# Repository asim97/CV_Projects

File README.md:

**WARNINIG**:
- this resp contains parts from bigger projects.
- this resp contains *only* embededd related projects, more projects are NOT included.
- *MOST* of libiries used in Skatchs are either modfied or originaly-writen to serve its pourpose in thier APP.
- no warranty grunted,use any parts of the code at your OWN risk.

**REQUIRMMENTS**:
- NI LABVIEW 2018
- Proutes 8.6
- Autodesk Eagle 8.5.6
- Arduino IDE 1.8.10
- SkethUP 2017
- ECLIPSE 2018

**NOTE**
	I used Arduino IDE as my main IDE for its simpelsty and easyly to compile the code to AVRs,ARMs,ESPs ...
	Eclipse was used at first, for  SVN and github only 
	since i was working alone... no need for the heavy interface for ECLIPSE

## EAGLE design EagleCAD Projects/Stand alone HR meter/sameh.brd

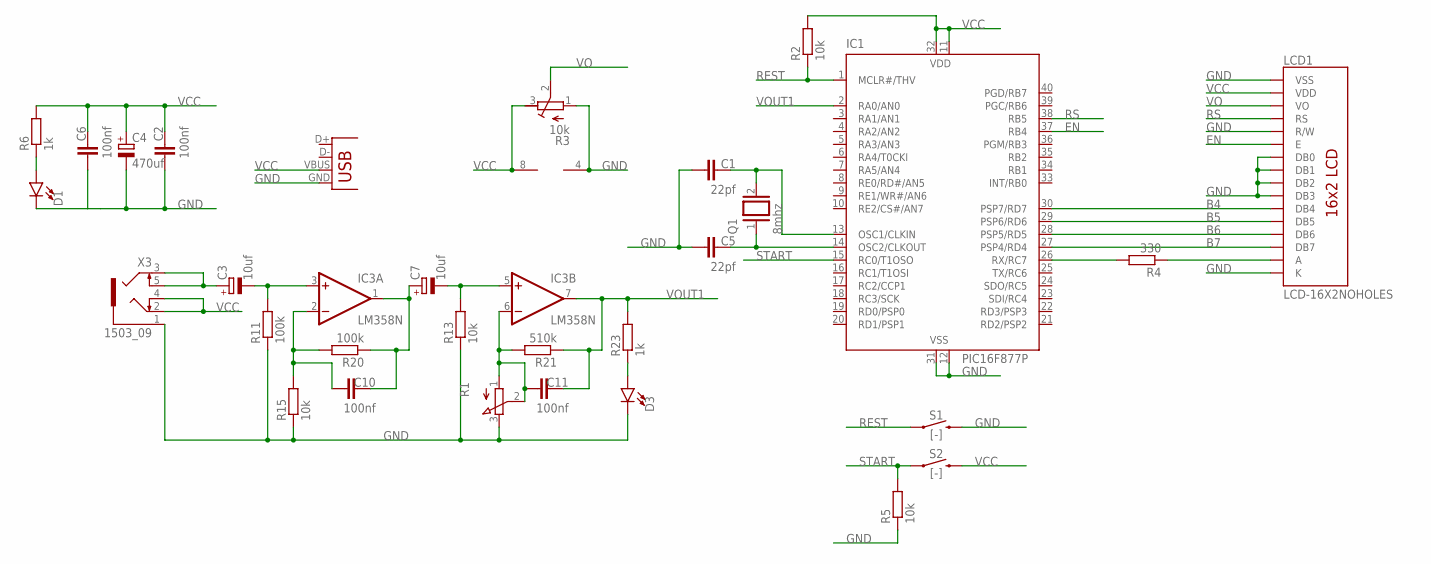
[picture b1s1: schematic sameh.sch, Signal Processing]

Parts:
C1, C5: 22pf; C050-030X075
C2, C6, C10, C11: 100nf; C050-030X075
C3, C7: 10uf; E2-5
C4: 470uf; E3,5-8
D1, D3: LED5MM; LED_5MM
IC1: PIC16F877P; DIL40
IC3: LM358N; DIL08
LCD1: LCD-16X2NOHOLES; LCD-16X2_NOHOLESNOSILK
Q1: 8mhz; QS
R1: 3RP/1610N
R2, R5, R13, R15: 10k; 0207/10
R3: 10k; RTRIM64W
R4: 330; 0207/10
R6, R23: 1k; 0207/10
R11, R20: 100k; 0207/10
R21: 510k; 0207/10
S1, S2: [-]; TACTILE_SWITCH_PTH_6.0MM
X2: USB-B-H
X3: 1503_09

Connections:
B4: IC1.30 (PSP7/RD7), LCD1.11 (DB4)
B5: IC1.29 (PSP6/RD6), LCD1.12 (DB5)
B6: IC1.28 (PSP5/RD5), LCD1.13 (DB6)
B7: IC1.27 (PSP4/RD4), LCD1.14 (DB7)
EN: IC1.37 (RB4), LCD1.6 (E)
GND: C1.1, C2.1, C4.-, C5.1, C6.1, D1.K (C), D3.K (C), IC1.12 (VSS), IC1.31 (VSS), IC3.4 (V-), LCD1.1 (VSS), LCD1.5 (R/W), LCD1.7 (DB0), LCD1.8 (DB1), LCD1.9 (DB2), LCD1.10 (DB3), LCD1.16 (K), R1.3 (E), R3.1 (A), R5.1, R11.1, R13.1, R15.1, S1.3 (2), X2.GND, X3.1
unnamed: C1.2, IC1.13 (OSC1/CLKIN), Q1.2
unnamed: C5.2, IC1.14 (OSC2/CLKOUT), Q1.1
unnamed: IC1.26 (RX/RC7), R4.2
unnamed: LCD1.15 (A), R4.1
unnamed: D1.A, R6.1
unnamed: C7.+, C10.2, IC3.1 (OUT), R20.1
unnamed: C10.1, IC3.2 (-IN), R15.2, R20.2
unnamed: C11.1, IC3.6 (-IN), R1.1 (A), R1.2 (S), R21.2
unnamed: C3.+, X3.3, X3.5
unnamed: C7.-, IC3.5 (+IN), R13.2
unnamed: C3.-, IC3.3 (+IN), R11.2
unnamed: D3.A, R23.1
REST: IC1.1 (MCLR#/THV), R2.1, S1.1
RS: IC1.38 (RB5), LCD1.4 (RS)
START: IC1.15 (RC0/T1OSO), R5.2, S2.1
VCC: C2.2, C4.+, C6.2, IC1.11 (VDD), IC1.32 (VDD), IC3.8 (V+), LCD1.2 (VDD), R2.2, R3.3 (E), R6.2, S2.3 (2), X2.VBUS, X3.2, X3.4
VO: LCD1.3 (VO), R3.2 (S)
VOUT1: C11.2, IC1.2 (RA0/AN0), IC3.7 (OUT), R21.1, R23.2

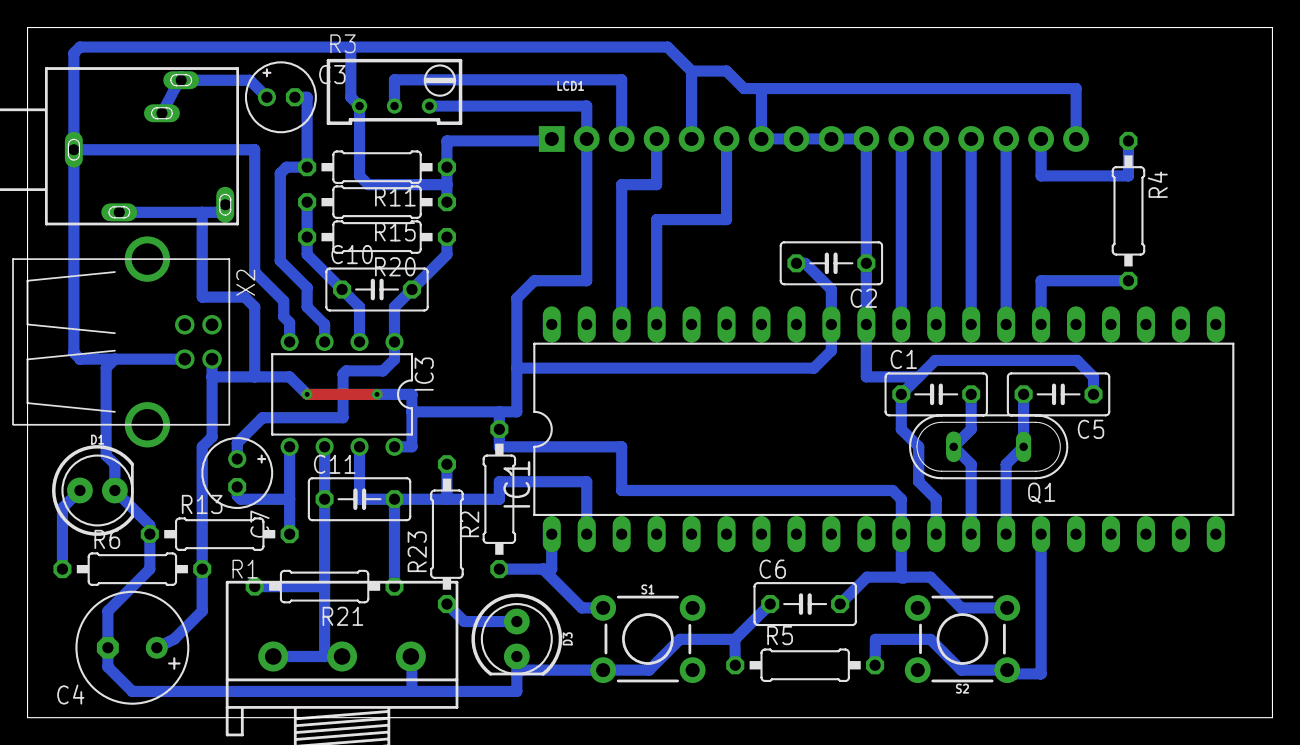
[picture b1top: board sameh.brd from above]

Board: 2 copper layers, 90.5 x 50.2 mm, 31 parts (0 on the bottom side), 24 nets.

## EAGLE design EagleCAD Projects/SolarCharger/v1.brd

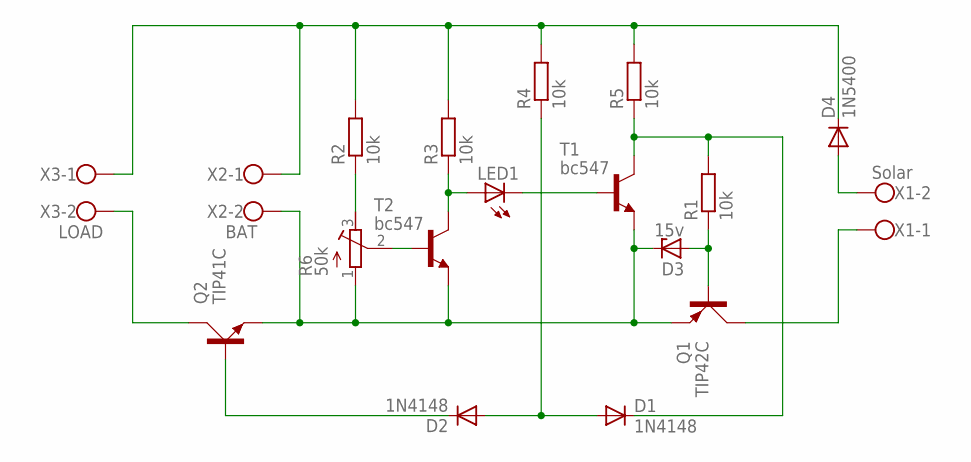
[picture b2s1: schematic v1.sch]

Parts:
D1, D2: 1N4148; DO35-10
D3: 15v; ZDIO-10
D4: 1N5400; DO201-15
LED1: LED5MM
Q1: TIP42C; TO220AV
Q2: TIP41C; TO220AV
R1, R2, R3, R4, R5: 10k; 0207/10
R6: 50k; RTRIM64W
T1, T2: bc547; TO92-CBE
X1: Solar; W237-102
X2: BAT; W237-102
X3: LOAD; W237-102

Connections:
GND: D3.C, Q1.E, Q2.E, R6.1 (A), T1.E, T2.E, X2.2
unnamed: R6.2 (S), T2.B
unnamed: R2.1, R6.3 (E)
unnamed: LED1.A, R3.1, T2.C
unnamed: LED1.K (C), T1.B
unnamed: D1.C, R1.2, R5.1, T1.C
unnamed: D3.A, Q1.B, R1.1
unnamed: D1.A, D2.A, R4.1
unnamed: Q2.C, X3.2
unnamed: Q1.C, X1.1
unnamed: D2.C, Q2.B
unnamed: D4.C, R2.2, R3.2, R4.2, R5.2, X2.1, X3.1
unnamed: D4.A, X1.2

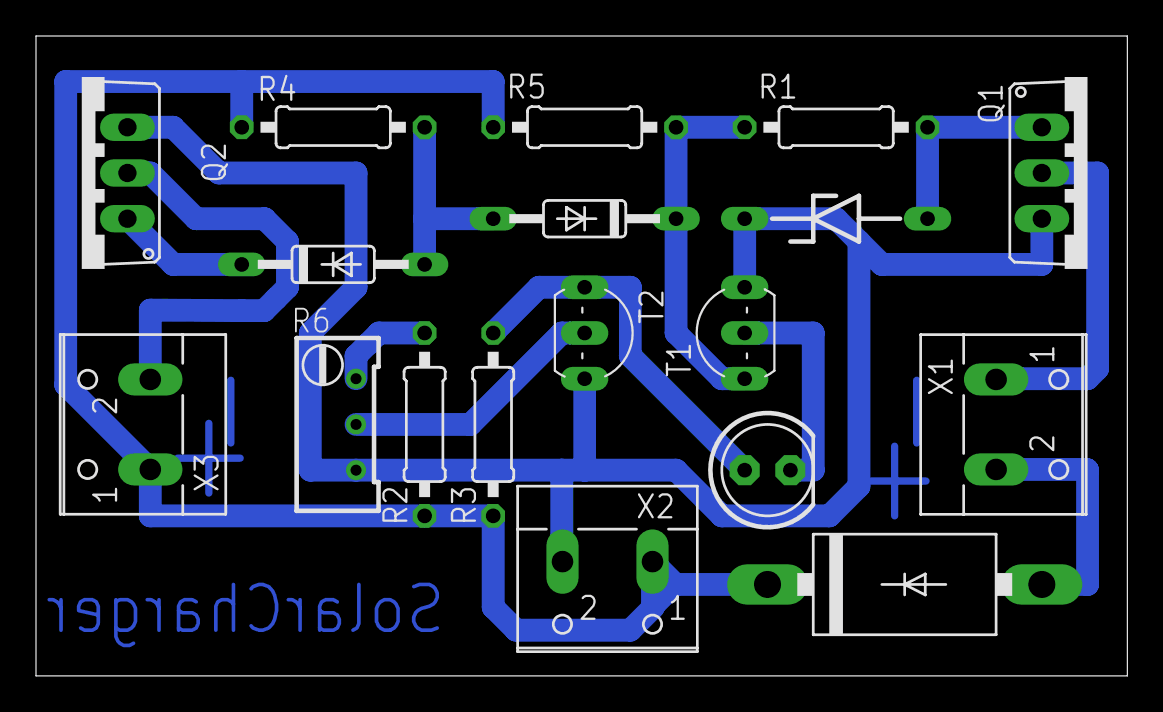
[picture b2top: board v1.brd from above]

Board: 2 copper layers, 60.6 x 35.5 mm, 18 parts (0 on the bottom side), 13 nets.

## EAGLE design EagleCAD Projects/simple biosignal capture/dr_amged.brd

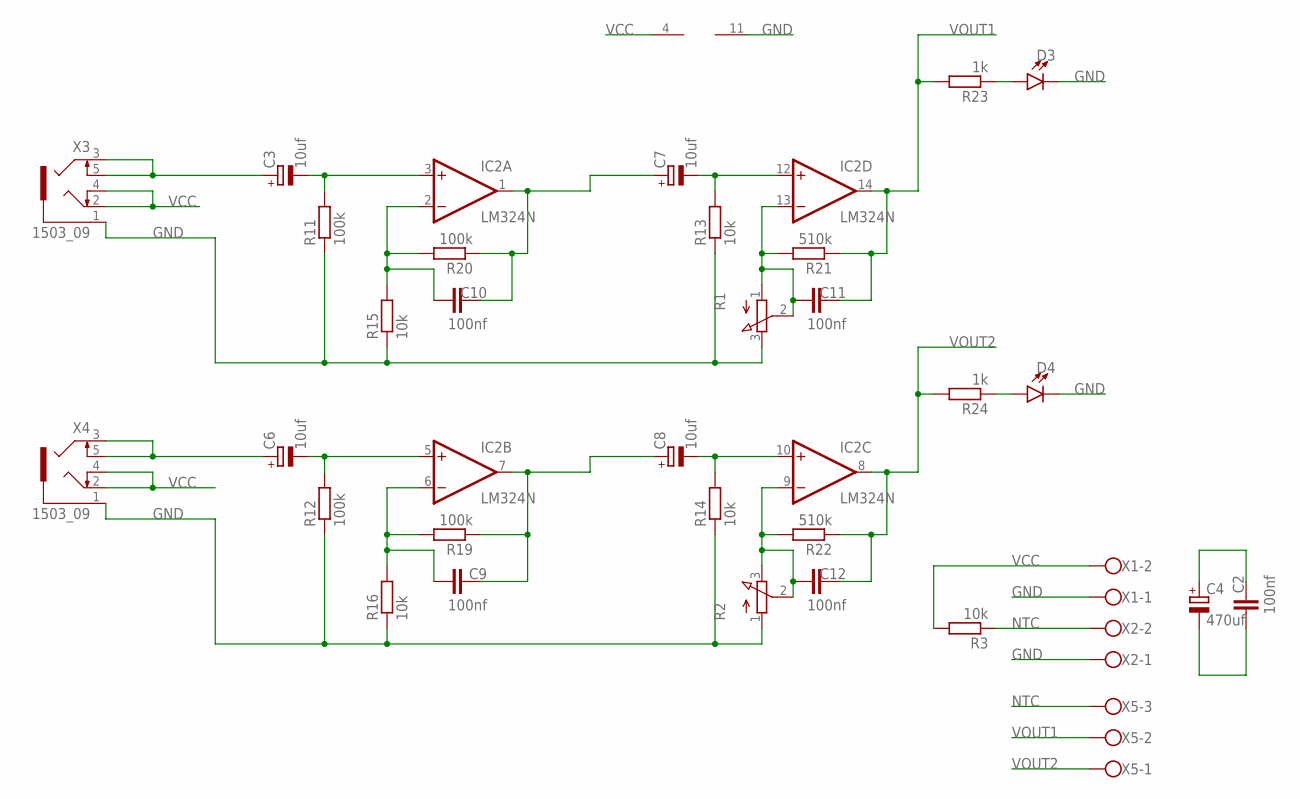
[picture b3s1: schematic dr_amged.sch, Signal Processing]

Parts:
C2, C9, C10, C11, C12: 100nf; C050-030X075
C3, C6, C7, C8: 10uf; E2-5
C4: 470uf; E3,5-8
D3, D4: LED5MM; LED_5MM
IC2: LM324N; DIL14
R1, R2: 3RP/1610N
R3, R13, R14, R15, R16: 10k; 0207/10
R11, R12, R19, R20: 100k; 0207/10
R21, R22: 510k; 0207/10
R23, R24: 1k; 0207/10
X1, X2: W237-102
X3, X4: 1503_09
X5: W237-103

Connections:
GND: C2.1, C4.-, D3.K (C), D4.K (C), IC2.11 (V-), R1.3 (E), R2.1 (A), R11.1, R12.1, R13.1, R14.1, R15.1, R16.1, X1.1, X2.1, X3.1, X4.1
unnamed: C8.+, C9.2, IC2.7 (OUT), R19.1
unnamed: C9.1, IC2.6 (-IN), R16.2, R19.2
unnamed: C7.+, C10.2, IC2.1 (OUT), R20.1
unnamed: C10.1, IC2.2 (-IN), R15.2, R20.2
unnamed: C11.1, IC2.13 (-IN), R1.1 (A), R1.2 (S), R21.2
unnamed: C12.1, IC2.9 (-IN), R2.2 (S), R2.3 (E), R22.2
unnamed: C6.+, X4.3, X4.5
unnamed: C3.+, X3.3, X3.5
unnamed: C6.-, IC2.5 (+IN), R12.2
unnamed: C7.-, IC2.12 (+IN), R13.2
unnamed: C8.-, IC2.10 (+IN), R14.2
unnamed: C3.-, IC2.3 (+IN), R11.2
unnamed: D3.A, R23.1
unnamed: D4.A, R24.1
NTC: R3.1, X2.2, X5.3
VCC: C2.2, C4.+, IC2.4 (V+), R3.2, X1.2, X3.2, X3.4, X4.2, X4.4
VOUT1: C11.2, IC2.14 (OUT), R21.1, R23.2, X5.2
VOUT2: C12.2, IC2.8 (OUT), R22.1, R24.2, X5.1

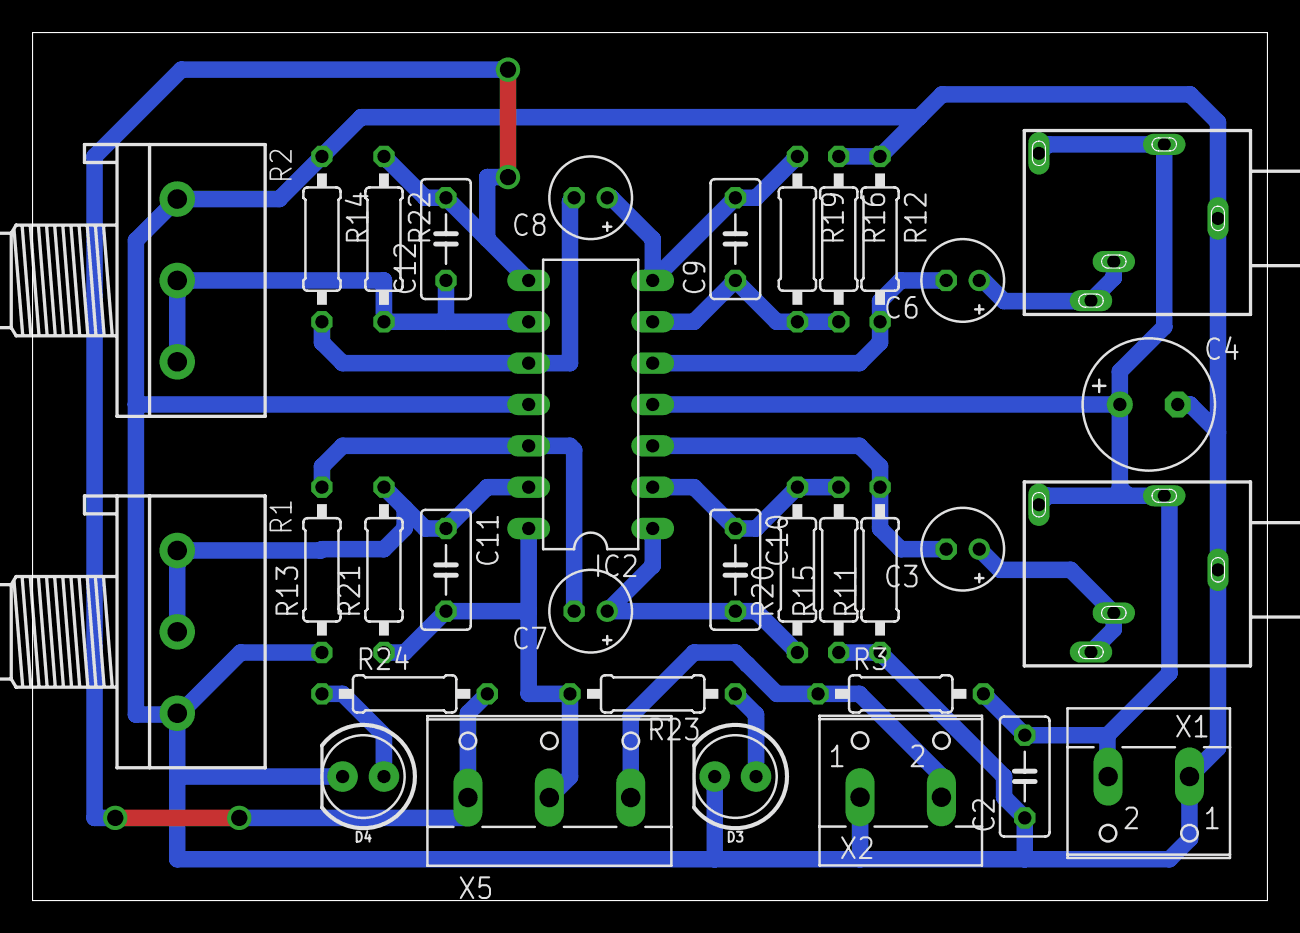
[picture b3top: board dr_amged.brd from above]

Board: 2 copper layers, 75.9 x 53.3 mm, 33 parts (0 on the bottom side), 19 nets.

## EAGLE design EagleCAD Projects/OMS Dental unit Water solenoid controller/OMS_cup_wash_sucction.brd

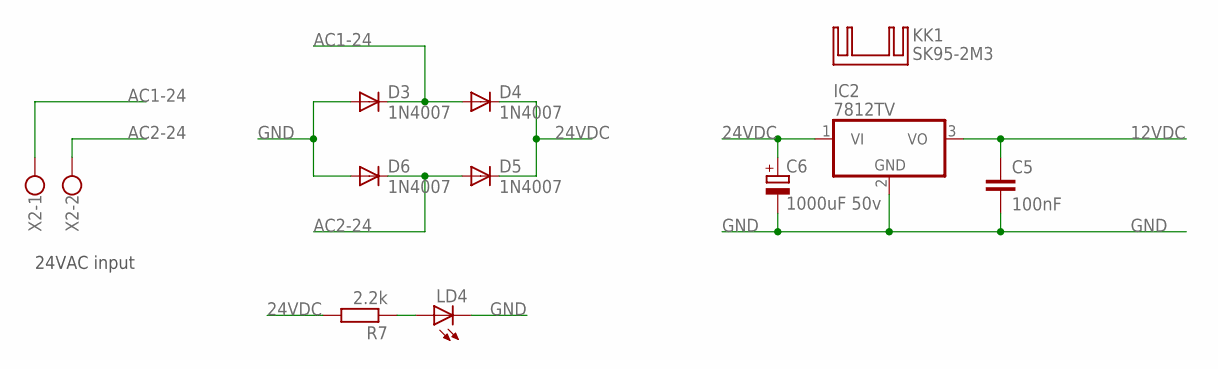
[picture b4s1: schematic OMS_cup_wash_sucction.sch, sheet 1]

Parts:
C5: 100nF; C050-025X075
C6: 1000uF 50v; E5-13
D3, D4, D5, D6: 1N4007; DO41-10
IC2: 7812TV; TO220V
KK1: SK95-2M3
LD4: LED5MM
R7: 2.2k; 0207/10
X2: W237-102

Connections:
12VDC: C5.1, IC2.3 (VO); also elsewhere on the board
24VDC: C6.+, D4.C, D5.C, IC2.1 (VI), R7.2; also elsewhere on the board
AC1-24: D3.C, D4.A, X2.1; also elsewhere on the board
AC2-24: D5.A, D6.C, X2.2; also elsewhere on the board
GND: C5.2, C6.-, D3.A, D6.A, IC2.2 (GND), LD4.K (C); also elsewhere on the board
unnamed: LD4.A, R7.1

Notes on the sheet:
24VAC input

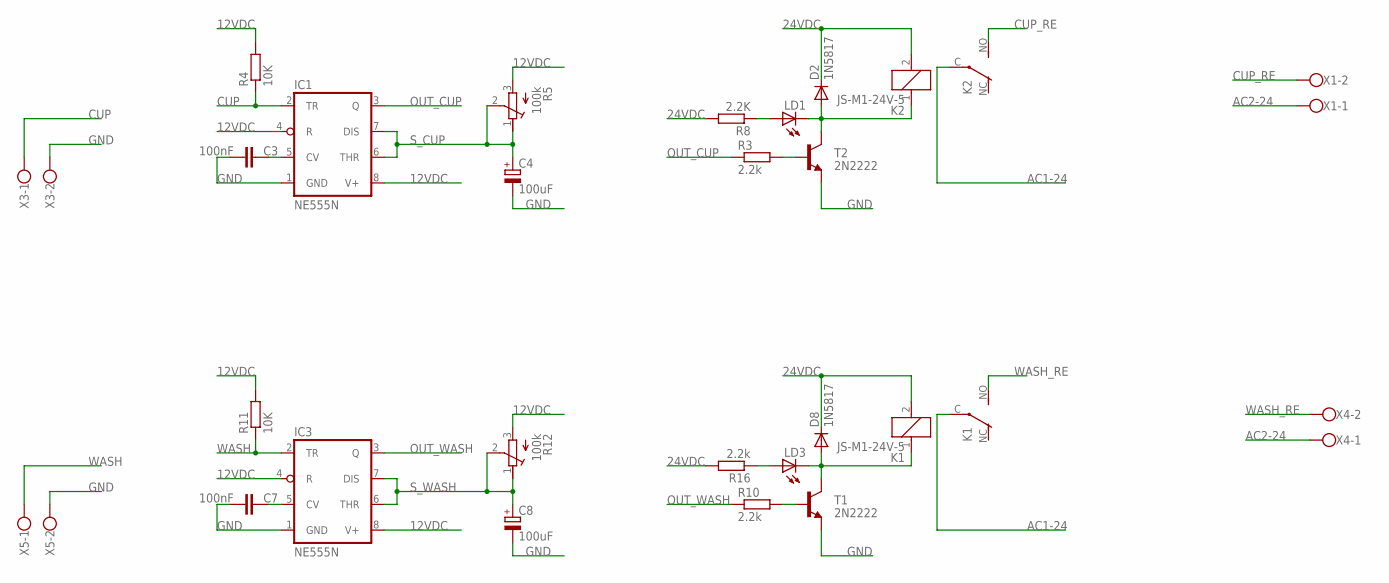
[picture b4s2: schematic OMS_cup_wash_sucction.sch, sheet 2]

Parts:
C3, C7: 100nF; C050-025X075
C4, C8: 100uF; E3,5-8
D2, D8: 1N5817; DO41-10
IC1, IC3: NE555N; DIL08-ROUND
K1, K2: JS-M1-24V-5; JS-M
LD1, LD3: LED5MM
R3, R10, R16: 2.2k; 0207/10
R4, R11: 10K; 0207/10
R5, R12: 100k; RTRIMT93XA
R8: 2.2K; 0207/10
T1, T2: 2N2222; TO92-EBC-OVAL
X1, X3, X4, X5: W237-102

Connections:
12VDC: IC1.4 (R), IC1.8 (V+), IC3.4 (R), IC3.8 (V+), R4.2, R5.3 (A), R11.2, R12.3 (A); also elsewhere on the board
24VDC: D2.C, D8.C, K1.2, K2.2, R8.2, R16.2; also elsewhere on the board
AC1-24: K1.C, K2.C; also elsewhere on the board
AC2-24: X1.1, X4.1; also elsewhere on the board
CUP: IC1.2 (TR), R4.1, X3.1
CUP_RE: K2.NO (S), X1.2
GND: C3.2, C4.-, C7.2, C8.-, IC1.1 (GND), IC3.1 (GND), T1.E, T2.E, X3.2, X5.2; also elsewhere on the board
unnamed: R3.2, T2.B
unnamed: C3.1, IC1.5 (CV)
unnamed: D2.A, K2.1, LD1.K (C), T2.C
unnamed: C7.1, IC3.5 (CV)
unnamed: LD1.A, R8.1
unnamed: D8.A, K1.1, LD3.K (C), T1.C
unnamed: R10.2, T1.B
unnamed: LD3.A, R16.1
OUT_CUP: IC1.3 (Q), R3.1
OUT_WASH: IC3.3 (Q), R10.1
S_CUP: C4.+, IC1.6 (THR), IC1.7 (DIS), R5.1 (E), R5.2 (S)
S_WASH: C8.+, IC3.6 (THR), IC3.7 (DIS), R12.1 (E), R12.2 (S)
WASH: IC3.2 (TR), R11.1, X5.1
WASH_RE: K1.NO (S), X4.2

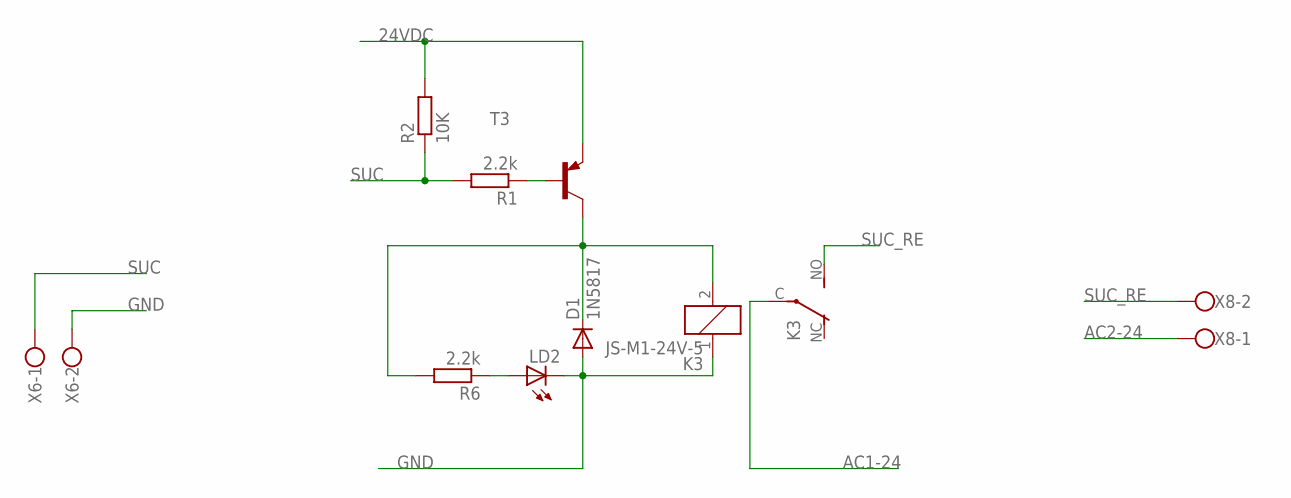
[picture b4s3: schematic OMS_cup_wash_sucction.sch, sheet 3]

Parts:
D1: 1N5817; DO41-10
K3: JS-M1-24V-5; JS-M
LD2: LED5MM
R1, R6: 2.2k; 0207/10
R2: 10K; 0207/10
T3: 2N5401-PNP-TO92-EBC; TO92-EBC
X6, X8: W237-102

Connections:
24VDC: R2.2, T3.E; also elsewhere on the board
AC1-24: K3.C; also elsewhere on the board
AC2-24: X8.1; also elsewhere on the board
GND: D1.A, K3.1, LD2.K (C), X6.2; also elsewhere on the board
unnamed: R1.1, T3.B
unnamed: LD2.A, R6.1
NS1: D1.C, K3.2, R6.2, T3.C
SUC: R1.2, R2.1, X6.1
SUC_RE: K3.NO (S), X8.2

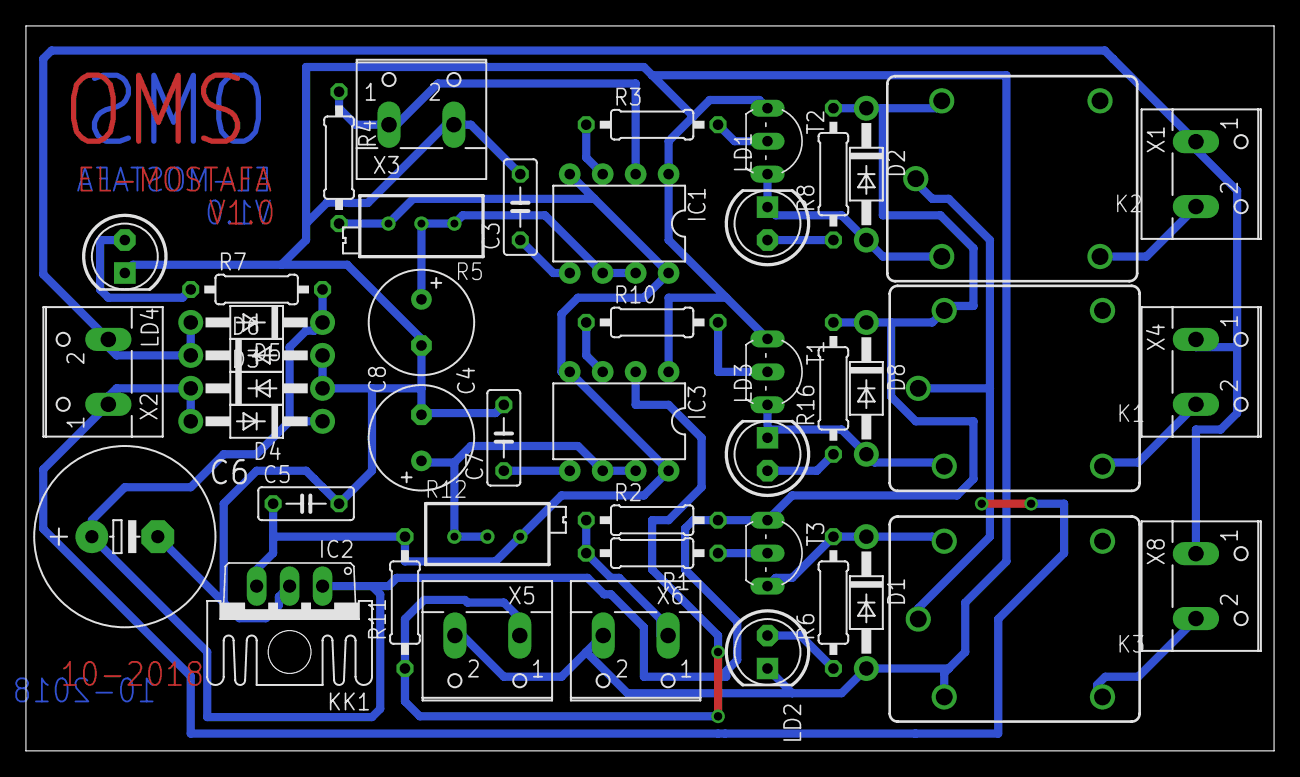
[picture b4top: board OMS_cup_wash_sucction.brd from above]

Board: 2 copper layers, 96.2 x 55.9 mm, 46 parts (0 on the bottom side), 27 nets.

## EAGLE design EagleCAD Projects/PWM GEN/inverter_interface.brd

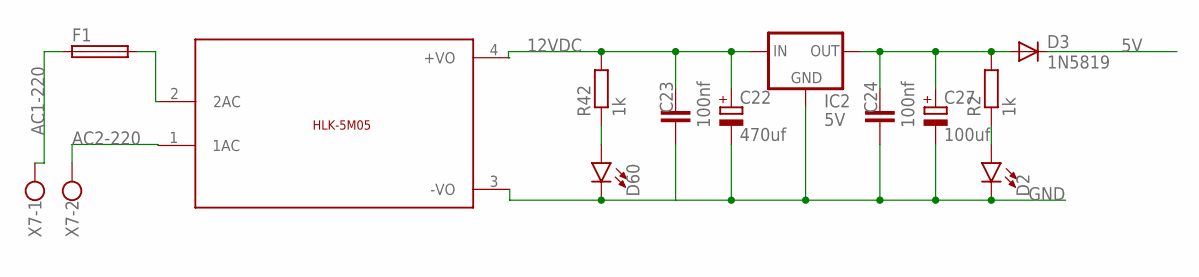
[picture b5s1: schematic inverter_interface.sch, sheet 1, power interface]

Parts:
C22: 470uf; E3,5-8
C23, C24: 100nf; C050-030X075
C27: 100uf; E3,5-8
D2, D60: LED5MM; LED_5MM
D3: 1N5819; DO41-10
F1: SHK20Q
IC2: 5V; 78XXL
R2, R42: 1k; 0207/10
U$3: 5VDC/5W; HLK-5M05
X7: W237-102

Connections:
5V: D3.C; also elsewhere on the board
12VDC: C22.+, C23.2, IC2.IN, R42.2, U$3.4 (+VO); also elsewhere on the board
AC1-220: F1.1A, X7.1
AC2-220: U$3.1 (1AC), X7.2
GND: C22.-, C23.1, C24.1, C27.-, D2.K (C), D60.K (C), IC2.GND, U$3.3 (-VO); also elsewhere on the board
unnamed: D2.A, R2.1
unnamed: C24.2, C27.+, D3.A, IC2.OUT, R2.2
unnamed: F1.2A, U$3.2 (2AC)
unnamed: D60.A, R42.1

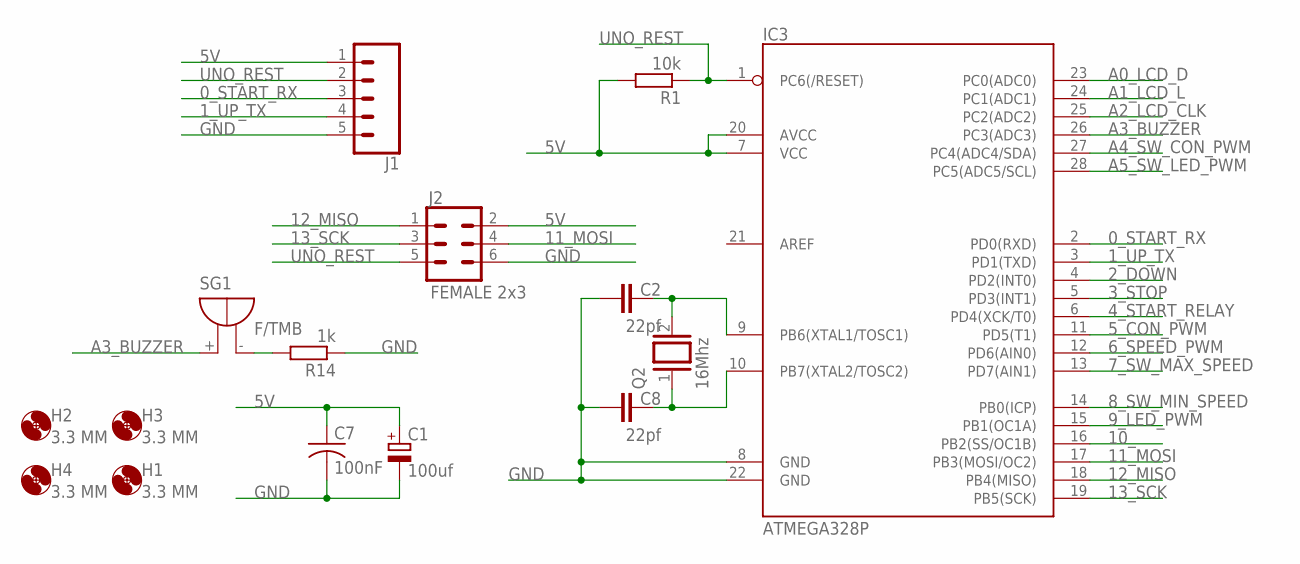
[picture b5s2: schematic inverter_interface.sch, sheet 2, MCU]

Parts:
C1: 100uf; E3,5-8
C2, C8: 22pf; C050-030X075
C7: 100nF; C050-035X075
H1, H2, H3, H4: 3.3 MM; 3,3
IC3: ATMEGA328P; DIL-28-3
J1: CONN_05JST-VERT; JST-5-PTH-VERT
J2: FEMALE 2x3; 2X3
Q2: 16Mhz; QS
R1: 10k; 0207/10
R14: 1k; 0207/10
SG1: F/TMB

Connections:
0_START_RX: IC3.2 (PD0(RXD)), J1.3; also elsewhere on the board
1_UP_TX: IC3.3 (PD1(TXD)), J1.4; also elsewhere on the board
2_DOWN: IC3.4 (PD2(INT0)); also elsewhere on the board
3_STOP: IC3.5 (PD3(INT1)); also elsewhere on the board
4_START_RELAY: IC3.6 (PD4(XCK/T0)); also elsewhere on the board
5V: C1.+, C7.1, IC3.7 (VCC), IC3.20 (AVCC), J1.1, J2.2, R1.2; also elsewhere on the board
5_CON_PWM: IC3.11 (PD5(T1)); also elsewhere on the board
6_SPEED_PWM: IC3.12 (PD6(AIN0)); also elsewhere on the board
7_SW_MAX_SPEED: IC3.13 (PD7(AIN1)); also elsewhere on the board
8_SW_MIN_SPEED: IC3.14 (PB0(ICP)); also elsewhere on the board
9_LED_PWM: IC3.15 (PB1(OC1A)); also elsewhere on the board
10_: IC3.16 (PB2(SS/OC1B))
11_MOSI: IC3.17 (PB3(MOSI/OC2)), J2.4
12_MISO: IC3.18 (PB4(MISO)), J2.1
13_SCK: IC3.19 (PB5(SCK)), J2.3
A0_LCD_D: IC3.23 (PC0(ADC0)); also elsewhere on the board
A1_LCD_L: IC3.24 (PC1(ADC1)); also elsewhere on the board
A2_LCD_CLK: IC3.25 (PC2(ADC2)); also elsewhere on the board
A3_BUZZER: IC3.26 (PC3(ADC3)), SG1.+
A4_SW_CON_PWM: IC3.27 (PC4(ADC4/SDA)); also elsewhere on the board
A5_SW_LED_PWM: IC3.28 (PC5(ADC5/SCL)); also elsewhere on the board
GND: C1.-, C2.1, C7.2, C8.1, IC3.8 (GND), IC3.22 (GND), J1.5, J2.6, R14.1; also elsewhere on the board
unnamed: C2.2, IC3.9 (PB6(XTAL1/TOSC1)), Q2.2
unnamed: C8.2, IC3.10 (PB7(XTAL2/TOSC2)), Q2.1
unnamed: R14.2, SG1.-
UNO_REST: IC3.1 (PC6(/RESET)), J1.2, J2.5, R1.1; also elsewhere on the board

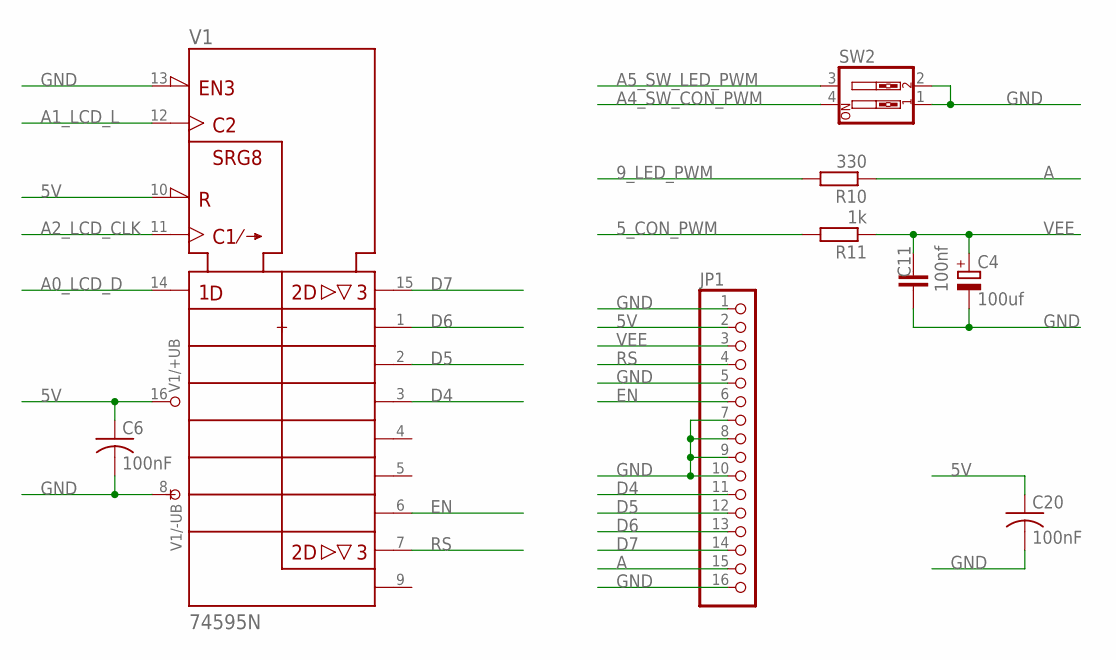
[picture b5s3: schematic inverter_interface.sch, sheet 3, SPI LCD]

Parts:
C4: 100uf; E3,5-8
C6, C20: 100nF; C050-035X075
C11: 100nf; C050-030X075
JP1: PINHD-1X16; 1X16
R10: 330; 0207/10
R11: 1k; 0207/10
SW2: SW_DIP-2; DIPSWITCH-02
V1: 74595N; DIL16

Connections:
5V: C6.1, C20.1, JP1.2, V1.10 (!SRCLR), V1.16 (+UB); also elsewhere on the board
5_CON_PWM: R11.2; also elsewhere on the board
9_LED_PWM: R10.2; also elsewhere on the board
A: JP1.15, R10.1
A0_LCD_D: V1.14 (SER); also elsewhere on the board
A1_LCD_L: V1.12 (RCK); also elsewhere on the board
A2_LCD_CLK: V1.11 (SRCK); also elsewhere on the board
A4_SW_CON_PWM: SW2.4; also elsewhere on the board
A5_SW_LED_PWM: SW2.3; also elsewhere on the board
D4: JP1.11, V1.3 (QD)
D5: JP1.12, V1.2 (QC)
D6: JP1.13, V1.1 (QB)
D7: JP1.14, V1.15 (QA)
EN: JP1.6, V1.6 (QG)
GND: C4.-, C6.2, C11.1, C20.2, JP1.1, JP1.5, JP1.7, JP1.8, JP1.9, JP1.10, JP1.16, SW2.1, SW2.2, V1.8 (-UB), V1.13 (!G); also elsewhere on the board
RS: JP1.4, V1.7 (QH)
VEE: C4.+, C11.2, JP1.3, R11.1

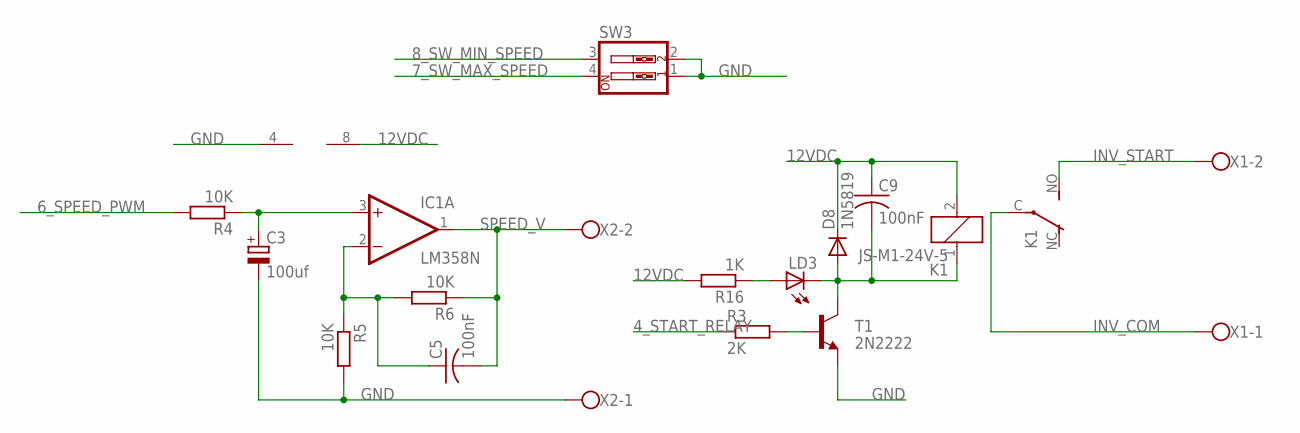
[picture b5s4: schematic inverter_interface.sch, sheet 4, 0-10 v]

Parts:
C3: 100uf; E3,5-8
C5, C9: 100nF; C050-035X075
D8: 1N5819; DO41-10
IC1: LM358N; DIL08
K1: JS-M1-24V-5; JS-M
LD3: LED5MM
R3: 2K; 0207/10
R4, R5, R6: 10K; 0207/10
R16: 1K; 0207/10
SW3: SW_DIP-2; DIPSWITCH-02
T1: 2N2222; TO92-EBC-OVAL
X1, X2: W237-102

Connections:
4_START_RELAY: R3.1; also elsewhere on the board
6_SPEED_PWM: R4.2; also elsewhere on the board
7_SW_MAX_SPEED: SW3.4; also elsewhere on the board
8_SW_MIN_SPEED: SW3.3; also elsewhere on the board
12VDC: C9.1, D8.C, IC1.8 (V+), K1.2, R16.2; also elsewhere on the board
GND: C3.-, IC1.4 (V-), R5.2, SW3.1, SW3.2, T1.E, X2.1; also elsewhere on the board
INV_COM: K1.C, X1.1
INV_START: K1.NO (S), X1.2
unnamed: C3.+, IC1.3 (+IN), R4.1
unnamed: C5.1, IC1.2 (-IN), R5.1, R6.2
unnamed: C9.2, D8.A, K1.1, LD3.K (C), T1.C
unnamed: R3.2, T1.B
unnamed: LD3.A, R16.1
SPEED_V: C5.2, IC1.1 (OUT), R6.1, X2.2

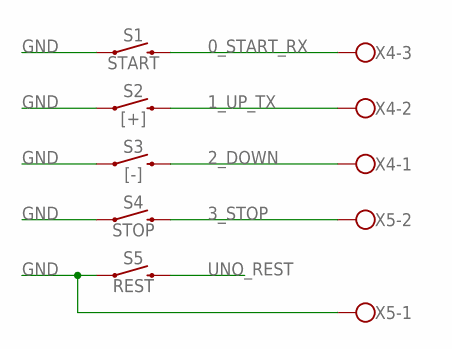
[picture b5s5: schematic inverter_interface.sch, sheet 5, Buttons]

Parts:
S1: START; TACTILE_SWITCH_PTH_6.0MM
S2: [+]; TACTILE_SWITCH_PTH_6.0MM
S3: [-]; TACTILE_SWITCH_PTH_6.0MM
S4: STOP; TACTILE_SWITCH_PTH_6.0MM
S5: REST; TACTILE_SWITCH_PTH_6.0MM
X4: W237-103
X5: W237-102

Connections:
0_START_RX: S1.3 (2), X4.3; also elsewhere on the board
1_UP_TX: S2.3 (2), X4.2; also elsewhere on the board
2_DOWN: S3.3 (2), X4.1; also elsewhere on the board
3_STOP: S4.3 (2), X5.2; also elsewhere on the board
GND: S1.1, S2.1, S3.1, S4.1, S5.1, X5.1; also elsewhere on the board
UNO_REST: S5.3 (2); also elsewhere on the board

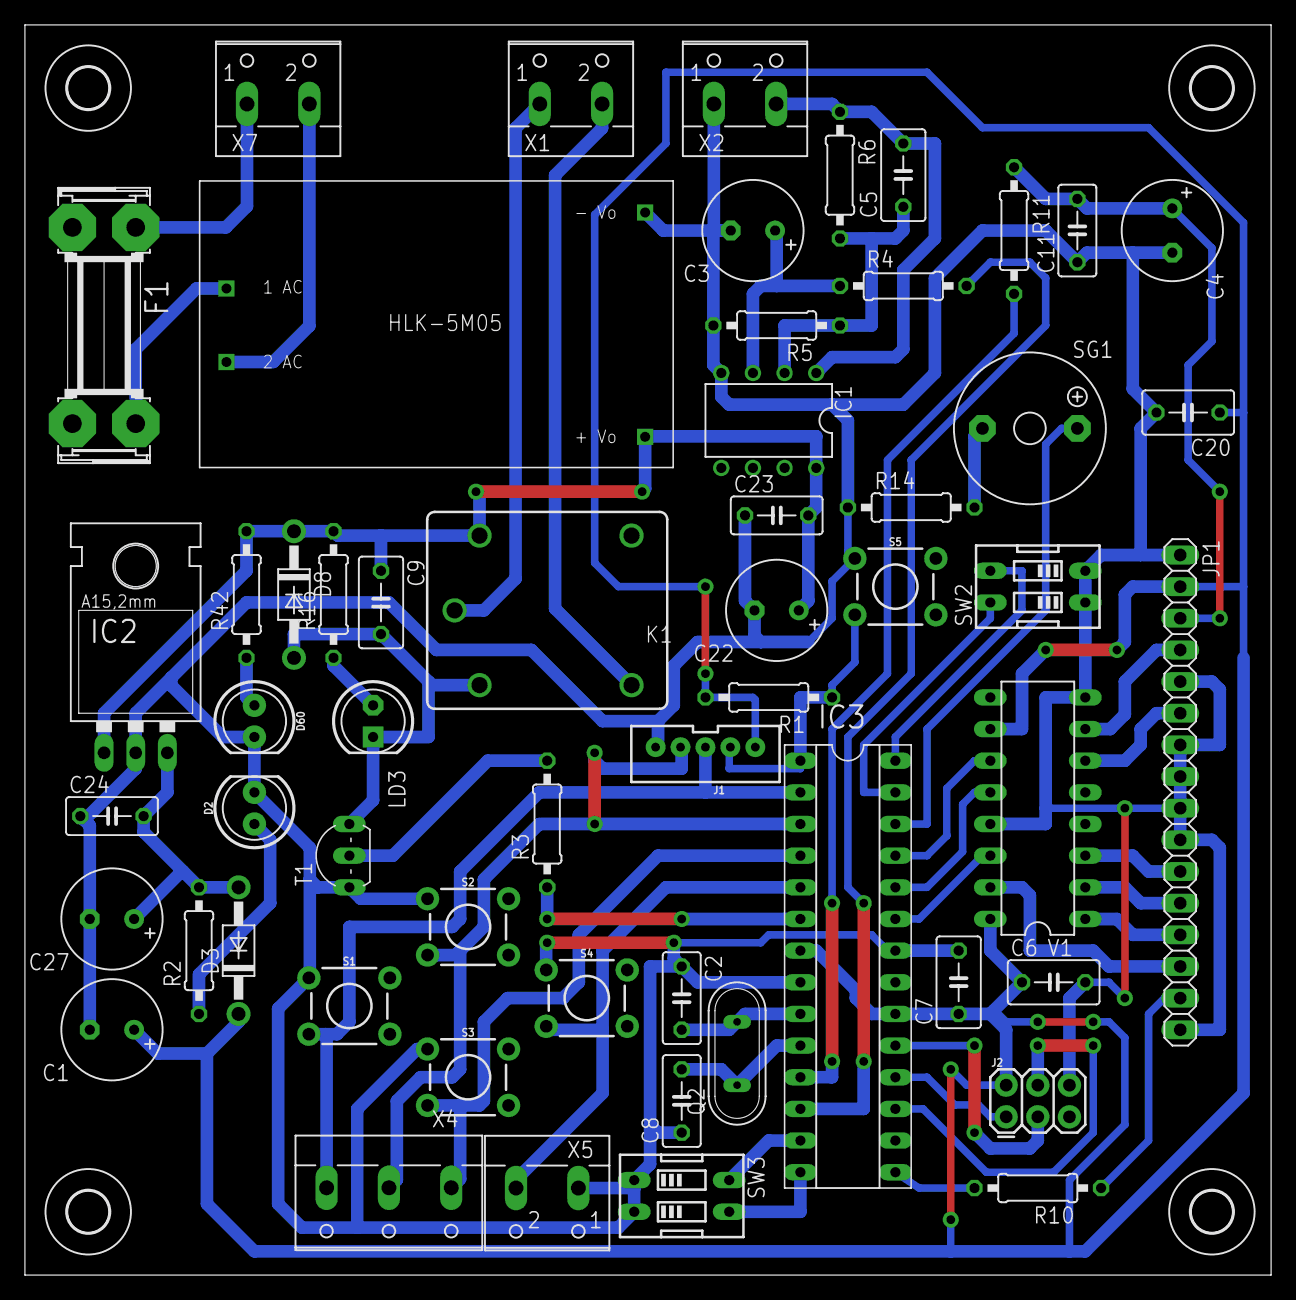
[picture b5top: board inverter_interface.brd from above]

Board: 2 copper layers, 100.0 x 100.3 mm, 60 parts (0 on the bottom side), 48 nets.

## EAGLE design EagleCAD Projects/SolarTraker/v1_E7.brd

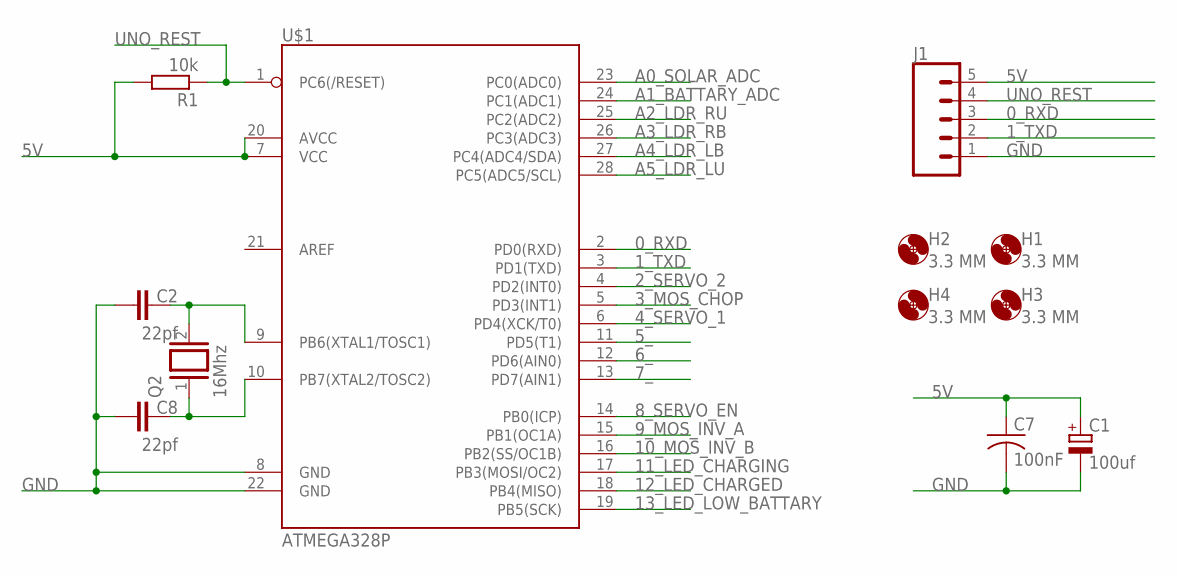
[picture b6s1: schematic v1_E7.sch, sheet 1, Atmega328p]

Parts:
C1: 100uf; E3,5-8
C2, C8: 22pf; C050-030X075
C7: 100nF; C050-035X075
H1, H2, H3, H4: 3.3 MM; 3,3
J1: CONN_05JST-VERT; JST-5-PTH-VERT
Q2: 16Mhz; QS
R1: 10k; 0207/10
U$1: ATMEGA328P; DIL-28-3

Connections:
0_RXD: J1.3, U$1.2 (PD0(RXD))
1_TXD: J1.2, U$1.3 (PD1(TXD))
2_SERVO_2: U$1.4 (PD2(INT0)); also elsewhere on the board
3_MOS_CHOP: U$1.5 (PD3(INT1)); also elsewhere on the board
4_SERVO_1: U$1.6 (PD4(XCK/T0)); also elsewhere on the board
5V: C1.+, C7.1, J1.5, R1.2, U$1.7 (VCC), U$1.20 (AVCC); also elsewhere on the board
5_: U$1.11 (PD5(T1))
6_: U$1.12 (PD6(AIN0))
7_: U$1.13 (PD7(AIN1))
8_SERVO_EN: U$1.14 (PB0(ICP)); also elsewhere on the board
9_MOS_INV_A: U$1.15 (PB1(OC1A)); also elsewhere on the board
10_MOS_INV_B: U$1.16 (PB2(SS/OC1B)); also elsewhere on the board
11_LED_CHARGING: U$1.17 (PB3(MOSI/OC2)); also elsewhere on the board
12_LED_CHARGED: U$1.18 (PB4(MISO)); also elsewhere on the board
13_LED_LOW_BATTARY: U$1.19 (PB5(SCK)); also elsewhere on the board
A0_SOLAR_ADC: U$1.23 (PC0(ADC0)); also elsewhere on the board
A1_BATTARY_ADC: U$1.24 (PC1(ADC1)); also elsewhere on the board
A2_LDR_RU: U$1.25 (PC2(ADC2)); also elsewhere on the board
A3_LDR_RB: U$1.26 (PC3(ADC3)); also elsewhere on the board
A4_LDR_LB: U$1.27 (PC4(ADC4/SDA)); also elsewhere on the board
A5_LDR_LU: U$1.28 (PC5(ADC5/SCL)); also elsewhere on the board
GND: C1.-, C2.1, C7.2, C8.1, J1.1, U$1.8 (GND), U$1.22 (GND); also elsewhere on the board
unnamed: C2.2, Q2.2, U$1.9 (PB6(XTAL1/TOSC1))
unnamed: C8.2, Q2.1, U$1.10 (PB7(XTAL2/TOSC2))
UNO_REST: J1.4, R1.1, U$1.1 (PC6(/RESET))

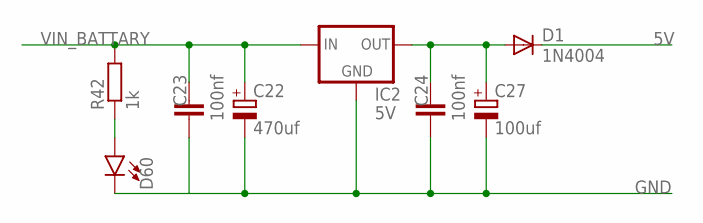
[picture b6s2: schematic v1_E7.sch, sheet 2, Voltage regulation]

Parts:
C22: 470uf; E3,5-8
C23, C24: 100nf; C050-030X075
C27: 100uf; E3,5-8
D1: 1N4004; DO41-10
D60: LED5MM; LED_5MM
IC2: 5V; 78XXL
R42: 1k; 0207/10

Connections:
5V: D1.C; also elsewhere on the board
GND: C22.-, C23.1, C24.1, C27.-, D60.K (C), IC2.GND; also elsewhere on the board
unnamed: C24.2, C27.+, D1.A, IC2.OUT
unnamed: D60.A, R42.1
VIN_BATTARY: C22.+, C23.2, IC2.IN, R42.2; also elsewhere on the board

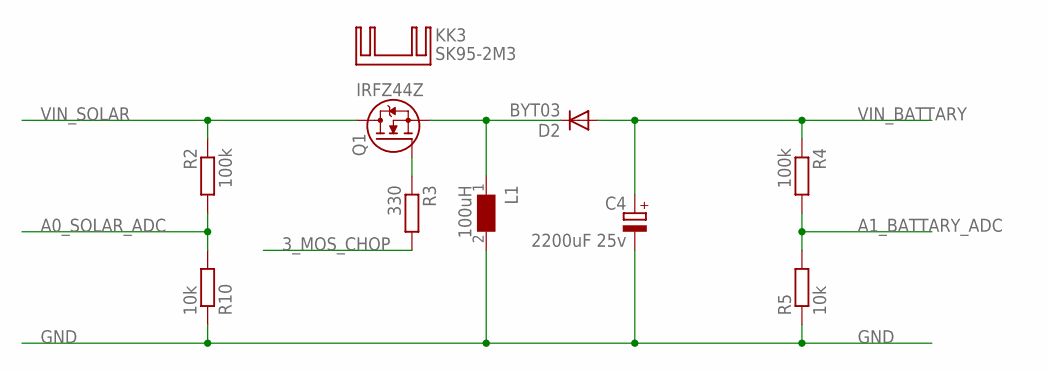
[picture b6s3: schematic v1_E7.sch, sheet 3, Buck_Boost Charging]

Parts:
C4: 2200uF 25v; E5-13
D2: BYT03; DO27-15
KK3: SK95-2M3
L1: 100uH; WE-ZB
Q1: IRFZ44Z; TO220V
R2, R4: 100k; 0207/10
R3: 330; 0207/10
R5, R10: 10k; 0207/10

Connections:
3_MOS_CHOP: R3.2; also elsewhere on the board
A0_SOLAR_ADC: R2.2, R10.2; also elsewhere on the board
A1_BATTARY_ADC: R4.2, R5.2; also elsewhere on the board
GND: C4.-, L1.2, R5.1, R10.1; also elsewhere on the board
unnamed: D2.C, L1.1, Q1.3 (S)
unnamed: Q1.1 (G), R3.1
VIN_BATTARY: C4.+, D2.A, R4.1; also elsewhere on the board
VIN_SOLAR: Q1.2 (D), R2.1; also elsewhere on the board

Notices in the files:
parts and their libraries:
SparkFun-LED: Licensing: Creative Commons ShareAlike 4.0 International - https://creativecommons.org/licenses/by-sa/4.0
wuerth_elektronik_eisos__v6.5: Copyright: Würth Elektronik
